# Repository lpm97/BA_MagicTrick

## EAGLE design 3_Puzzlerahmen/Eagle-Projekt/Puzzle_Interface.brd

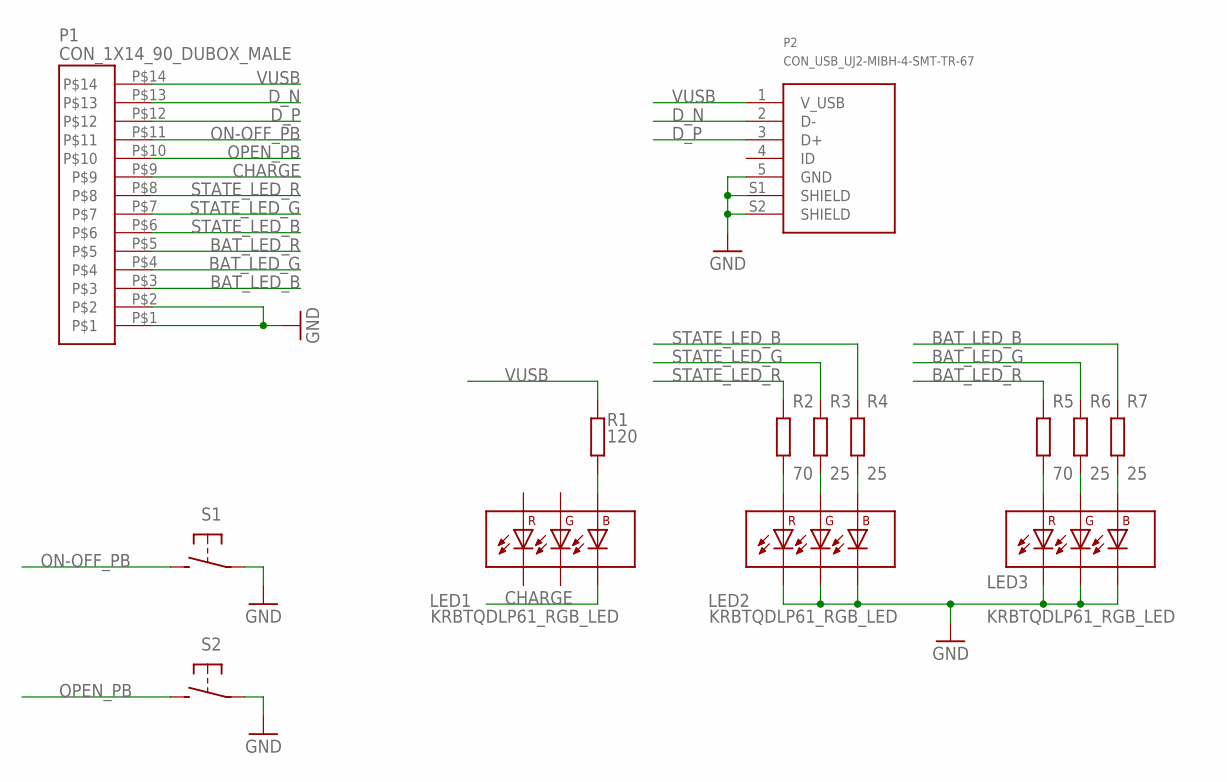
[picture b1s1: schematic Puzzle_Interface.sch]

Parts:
LED1, LED2, LED3: KRBTQDLP61_RGB_LED
P1: CON_1X14_90_DUBOX_MALE
P2: CON_USB_UJ2-MIBH-4-SMT-TR-67
R1: 120; 0603
R2, R5: 70; 0603
R3, R4, R6, R7: 25; 0603
S1, S2: EG5358CT-ND_PB

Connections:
BAT_LED_B: P1.P$3, R7.2
BAT_LED_G: P1.P$4, R6.2
BAT_LED_R: P1.P$5, R5.2
CHARGE: LED1.P$4 (BC), P1.P$9
D_N: P1.P$13, P2.2 (D-)
D_P: P1.P$12, P2.3 (D+)
GND: LED2.P$3 (GC), LED2.P$4 (BC), LED2.P$6 (RC), LED3.P$3 (GC), LED3.P$4 (BC), LED3.P$6 (RC), P1.P$1, P1.P$2, P2.5 (GND), P2.S1 (SHIELD), P2.S2 (SHIELD), S1.1, S1.S1, S1.S2, S2.1, S2.S1, S2.S2
unnamed: LED1.P$2 (BA), R1.1
unnamed: LED2.P$5 (RA), R2.1
unnamed: LED2.P$1 (GA), R3.1
unnamed: LED2.P$2 (BA), R4.1
unnamed: LED3.P$5 (RA), R5.1
unnamed: LED3.P$1 (GA), R6.1
unnamed: LED3.P$2 (BA), R7.1
ON-OFF_PB: P1.P$11, S1.2 (S)
OPEN_PB: P1.P$10, S2.2 (S)
STATE_LED_B: P1.P$6, R4.2
STATE_LED_G: P1.P$7, R3.2
STATE_LED_R: P1.P$8, R2.2
VUSB: P1.P$14, P2.1 (V_USB), R1.2

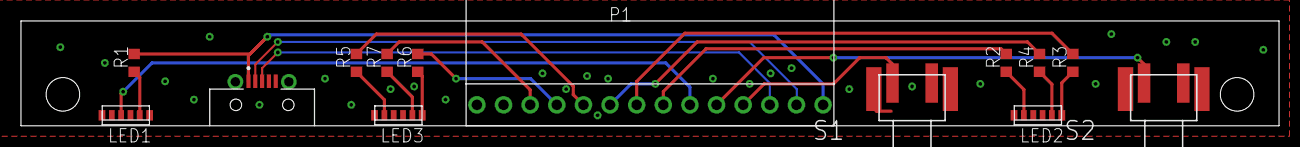
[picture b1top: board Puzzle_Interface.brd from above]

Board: 2 copper layers, 120.0 x 10.0 mm, 14 parts (0 on the bottom side), 20 nets.

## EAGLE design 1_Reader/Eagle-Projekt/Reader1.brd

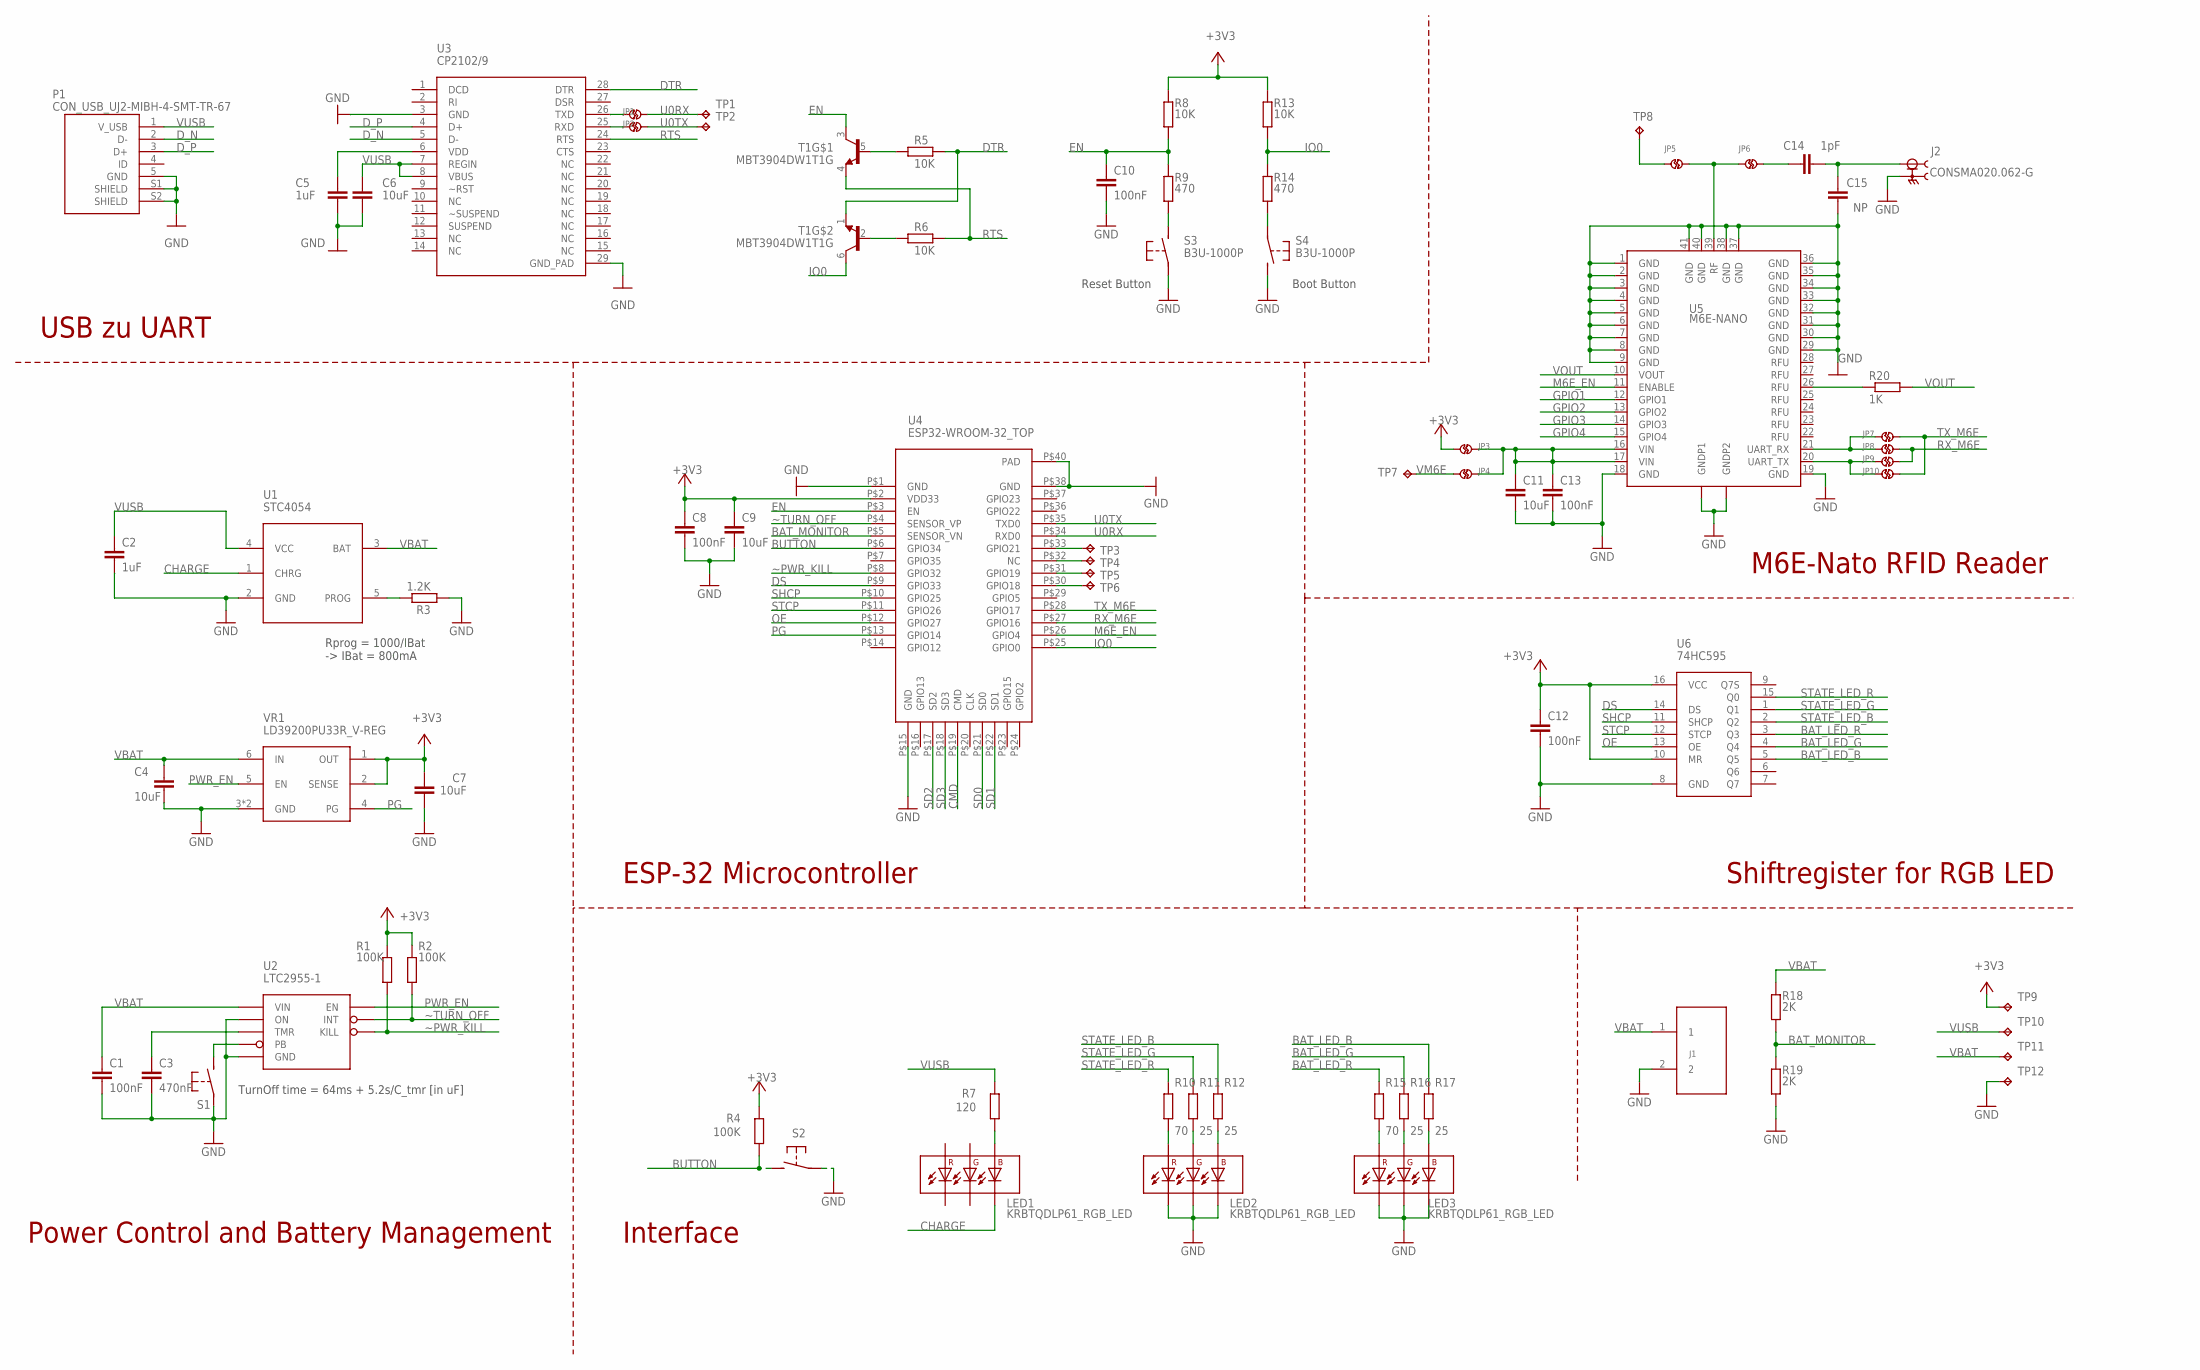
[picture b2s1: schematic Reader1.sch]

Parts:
C1, C8, C10, C12, C13: 100nF; 0603
C2, C5: 1uF; 0603
C3: 470nF; 0603
C4, C6, C7, C9, C11: 10uF; 0603
C14: 1pF; 0603
C15: NP; 0603
J1: CON_2
J2: CONSMA020.062-G; LINX_CONSMA020.062-G
JP1, JP2, JP3, JP4, JP5, JP6, JP7, JP8, JP9, JP10: SOLDER_JUMPER
LED1, LED2, LED3: KRBTQDLP61_RGB_LED
P1: CON_USB_UJ2-MIBH-4-SMT-TR-67
R1, R2, R4: 100K; 0603
R3: 1.2K; 0603
R5, R6, R8, R13: 10K; 0603
R7: 120; 0603
R9, R14: 470; 0603
R10, R15: 70; 0603
R11, R12, R16, R17: 25; 0603
R18, R19: 2K; 0603
R20: 1K; 0603
S1, S2: EG5358CT-ND_PB
S3, S4: B3U-1000P
T1: MBT3904DW1T1G; SOT23-6
TP1, TP2, TP3, TP4, TP5, TP6, TP7, TP8, TP9, TP10, TP11, TP12: TP; TEST_PAD
U1: STC4054; TSOT23-5L
U2: LTC2955-1; SOT23-8
U3: CP2102/9; QFN-28
U4: ESP32-WROOM-32_TOP
U5: M6E-NANO
U6: 74HC595; SOIC-16
VR1: LD39200PU33R_V-REG; DFN-6

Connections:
+3V3: C7.2, C8.1, C9.1, C12.1, JP3.P$1, R1.1, R2.1, R4.2, R8.2, R13.2, TP9.TP, U4.P$2 (VDD33), U6.10 (MR), U6.16 (VCC), VR1.1 (OUT), VR1.2 (SENSE)
BAT_LED_B: R17.2, U6.5 (Q5)
BAT_LED_G: R16.2, U6.4 (Q4)
BAT_LED_R: R15.2, U6.3 (Q3)
BAT_MONITOR: R18.2, R19.1, U4.P$5 (SENSOR_VN)
BUTTON: R4.1, S2.2 (S), U4.P$6 (GPIO34)
CHARGE: LED1.P$4 (BC), U1.1 (CHRG)
CMD: U4.P$19 (CMD)
DS: U4.P$9 (GPIO33), U6.14 (DS)
DTR: R5.1, T1.1 (E), U3.28 (DTR)
D_N: P1.2 (D-), U3.5 (D-)
D_P: P1.3 (D+), U3.4 (D+)
EN: C10.1, R8.1, R9.2, T1.3 (C), U4.P$3 (EN)
GND: C1.2, C2.2, C3.2, C4.2, C5.2, C6.2, C7.1, C8.2, C9.2, C10.2, C11.2, C12.2, C13.2, C15.1, J1.2, J2.S1 (2), J2.S2 (2), J2.S3 (2), J2.S4 (2), LED2.P$3 (GC), LED2.P$4 (BC), LED2.P$6 (RC), LED3.P$3 (GC), LED3.P$4 (BC), LED3.P$6 (RC), P1.5 (GND), P1.S1 (SHIELD), P1.S2 (SHIELD), R3.1, R19.2, S1.1, S1.S1, S1.S2, S2.1, S2.S1, S2.S2, S3.P$1, S4.P$2 (S), TP12.TP, U1.2 (GND), U2.1 (ON), U2.4 (GND), U3.3 (GND), U3.29 (GND_PAD), U4.P$1 (GND), U4.P$15 (GND), U4.P$38 (GND), U4.P$40 (PAD), U5.1 (GND), U5.2 (GND), U5.3 (GND), U5.4 (GND), U5.5 (GND), U5.6 (GND), U5.7 (GND), U5.8 (GND), U5.9 (GND), U5.18 (GND), U5.19 (GND), U5.29 (GND), U5.30 (GND), U5.31 (GND), U5.32 (GND), U5.33 (GND), U5.34 (GND), U5.35 (GND), U5.36 (GND), U5.37 (GND), U5.38 (GND), U5.40 (GND), U5.41 (GND), U5.GND_PAD1 (GNDP1), U5.GND_PAD2 (GNDP2), U6.8 (GND), VR1.3 (GND), VR1.7 (GND)
GPIO1: U5.12 (GPIO1)
GPIO2: U5.13 (GPIO2)
GPIO3: U5.14 (GPIO3)
GPIO4: U5.15 (GPIO4)
IO0: R13.1, R14.2, T1.6 (C), U4.P$25 (GPIO0)
M6E_EN: U4.P$26 (GPIO4), U5.11 (ENABLE)
unnamed: R20.1, U5.26 (RFU)
unnamed: JP5.P$2, JP6.P$1, U5.39 (RF)
unnamed: C14.1, JP6.P$2
unnamed: C14.2, C15.2, J2.1
unnamed: JP5.P$1, TP8.TP
unnamed: R5.2, T1.5 (B)
unnamed: R6.2, T1.2 (B)
unnamed: C5.1, U3.6 (VDD)
unnamed: LED3.P$5 (RA), R15.1
unnamed: R9.1, S3.P$2 (S)
unnamed: R14.1, S4.P$1
unnamed: C11.1, C13.1, JP3.P$2, JP4.P$2, U5.16 (VIN), U5.17 (VIN)
unnamed: LED2.P$5 (RA), R10.1
unnamed: LED1.P$2 (BA), R7.1
unnamed: LED2.P$1 (GA), R11.1
unnamed: LED2.P$2 (BA), R12.1
unnamed: LED3.P$1 (GA), R16.1
unnamed: R3.2, U1.5 (PROG)
unnamed: JP1.P$1, U3.26 (TXD)
unnamed: LED3.P$2 (BA), R17.1
unnamed: JP2.P$1, U3.25 (RXD)
unnamed: S1.2 (S), U2.5 (PB)
unnamed: TP5.TP, U4.P$31 (GPIO19)
unnamed: C3.1, U2.3 (TMR)
unnamed: TP6.TP, U4.P$30 (GPIO18)
unnamed: TP3.TP, U4.P$33 (GPIO21)
unnamed: TP4.TP, U4.P$32 (NC)
OE: U4.P$12 (GPIO27), U6.13 (OE)
PG: U4.P$13 (GPIO14), VR1.4 (PG)
PWR_EN: U2.7 (EN), VR1.5 (EN)
RTS: R6.1, T1.4 (E), U3.24 (RTS)
RXI: JP7.P$1, JP8.P$1, U5.21 (UART_RX)
RX_M6E: JP8.P$2, JP9.P$2, U4.P$27 (GPIO16)
SD0: U4.P$21 (SD0)
SD1: U4.P$22 (SD1)
SD2: U4.P$17 (SD2)
SD3: U4.P$18 (SD3)
SHCP: U4.P$10 (GPIO25), U6.11 (SHCP)
STATE_LED_B: R12.2, U6.2 (Q2)
STATE_LED_G: R11.2, U6.1 (Q1)
STATE_LED_R: R10.2, U6.15 (Q0)
STCP: U4.P$11 (GPIO26), U6.12 (STCP)
TXO: JP9.P$1, JP10.P$1, U5.20 (UART_TX)
TX_M6E: JP7.P$2, JP10.P$2, U4.P$28 (GPIO17)
U0RX: JP1.P$2, TP1.TP, U4.P$34 (RXD0)
U0TX: JP2.P$2, TP2.TP, U4.P$35 (TXD0)
VBAT: C1.1, C4.1, J1.1, R18.1, TP11.TP, U1.3 (BAT), U2.6 (VIN), VR1.6 (IN)
VM6E: JP4.P$1, TP7.TP
VOUT: R20.2, U5.10 (VOUT)
VUSB: C2.1, C6.1, P1.1 (V_USB), R7.2, TP10.TP, U1.4 (VCC), U3.7 (REGIN), U3.8 (VBUS)
~PWR_KILL: R1.2, U2.2 (KILL), U4.P$8 (GPIO32)
~TURN_OFF: R2.2, U2.8 (INT), U4.P$4 (SENSOR_VP)

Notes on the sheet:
Rprog = 1000/IBat -> IBat = 800mA
TurnOff time = 64ms + 5.2s/C_tmr [in uF]
Reset Button
Boot Button
Power Control and Battery Management
ESP-32 Microcontroller
USB zu UART
Interface
Shiftregister for RGB LED
M6E-Nato RFID Reader

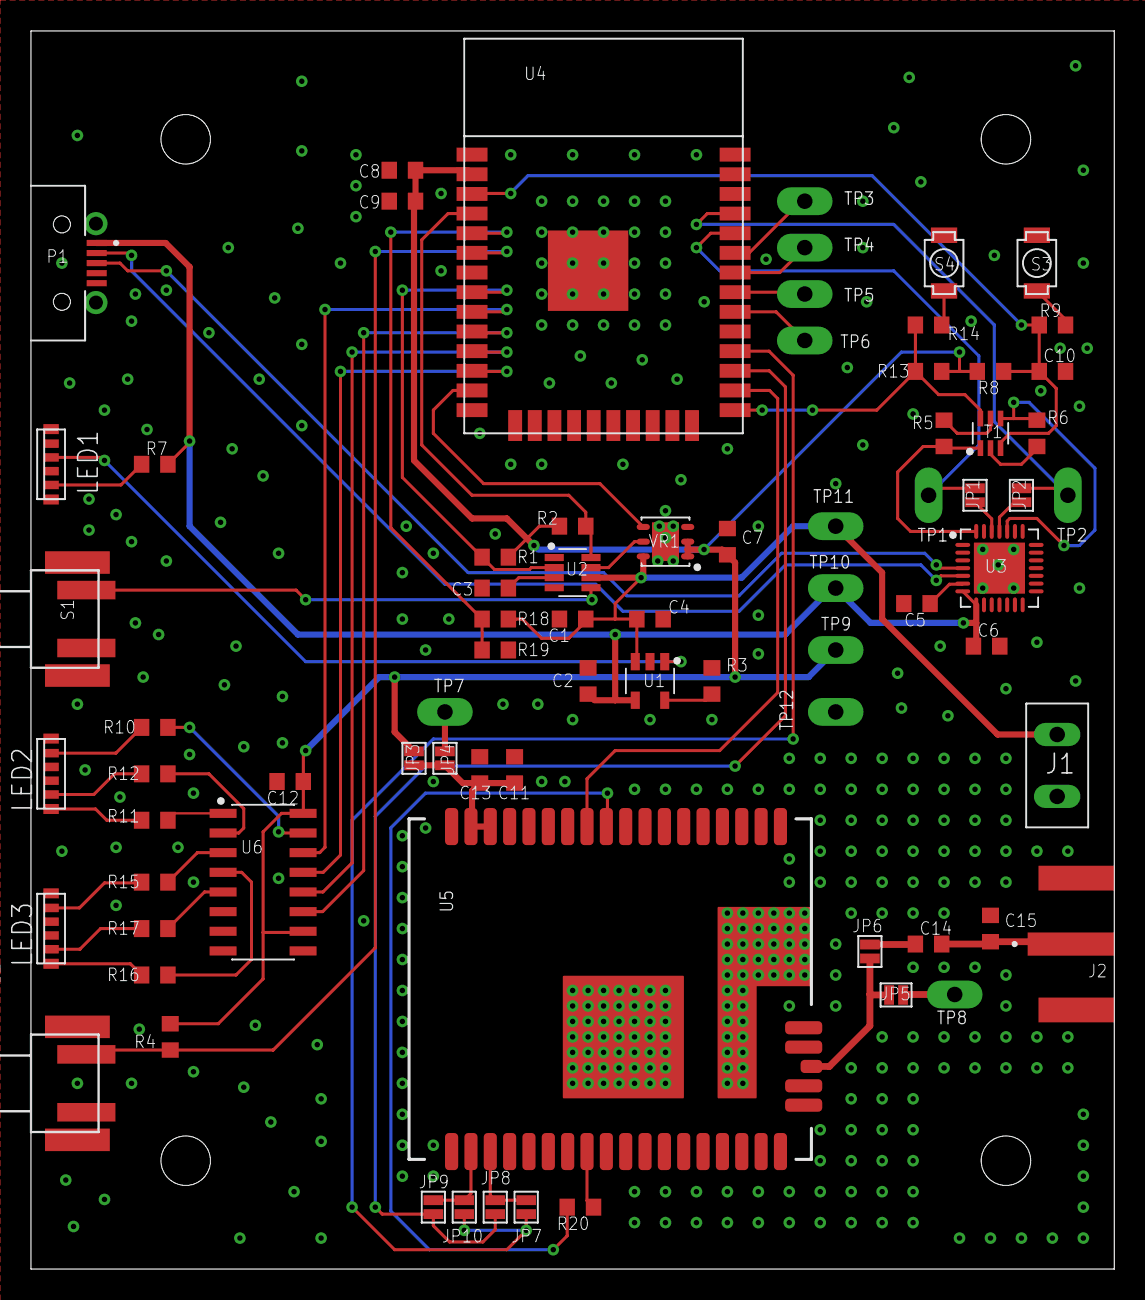
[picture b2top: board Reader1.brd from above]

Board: 2 copper layers, 70.0 x 80.0 mm, 75 parts (0 on the bottom side), 63 nets.

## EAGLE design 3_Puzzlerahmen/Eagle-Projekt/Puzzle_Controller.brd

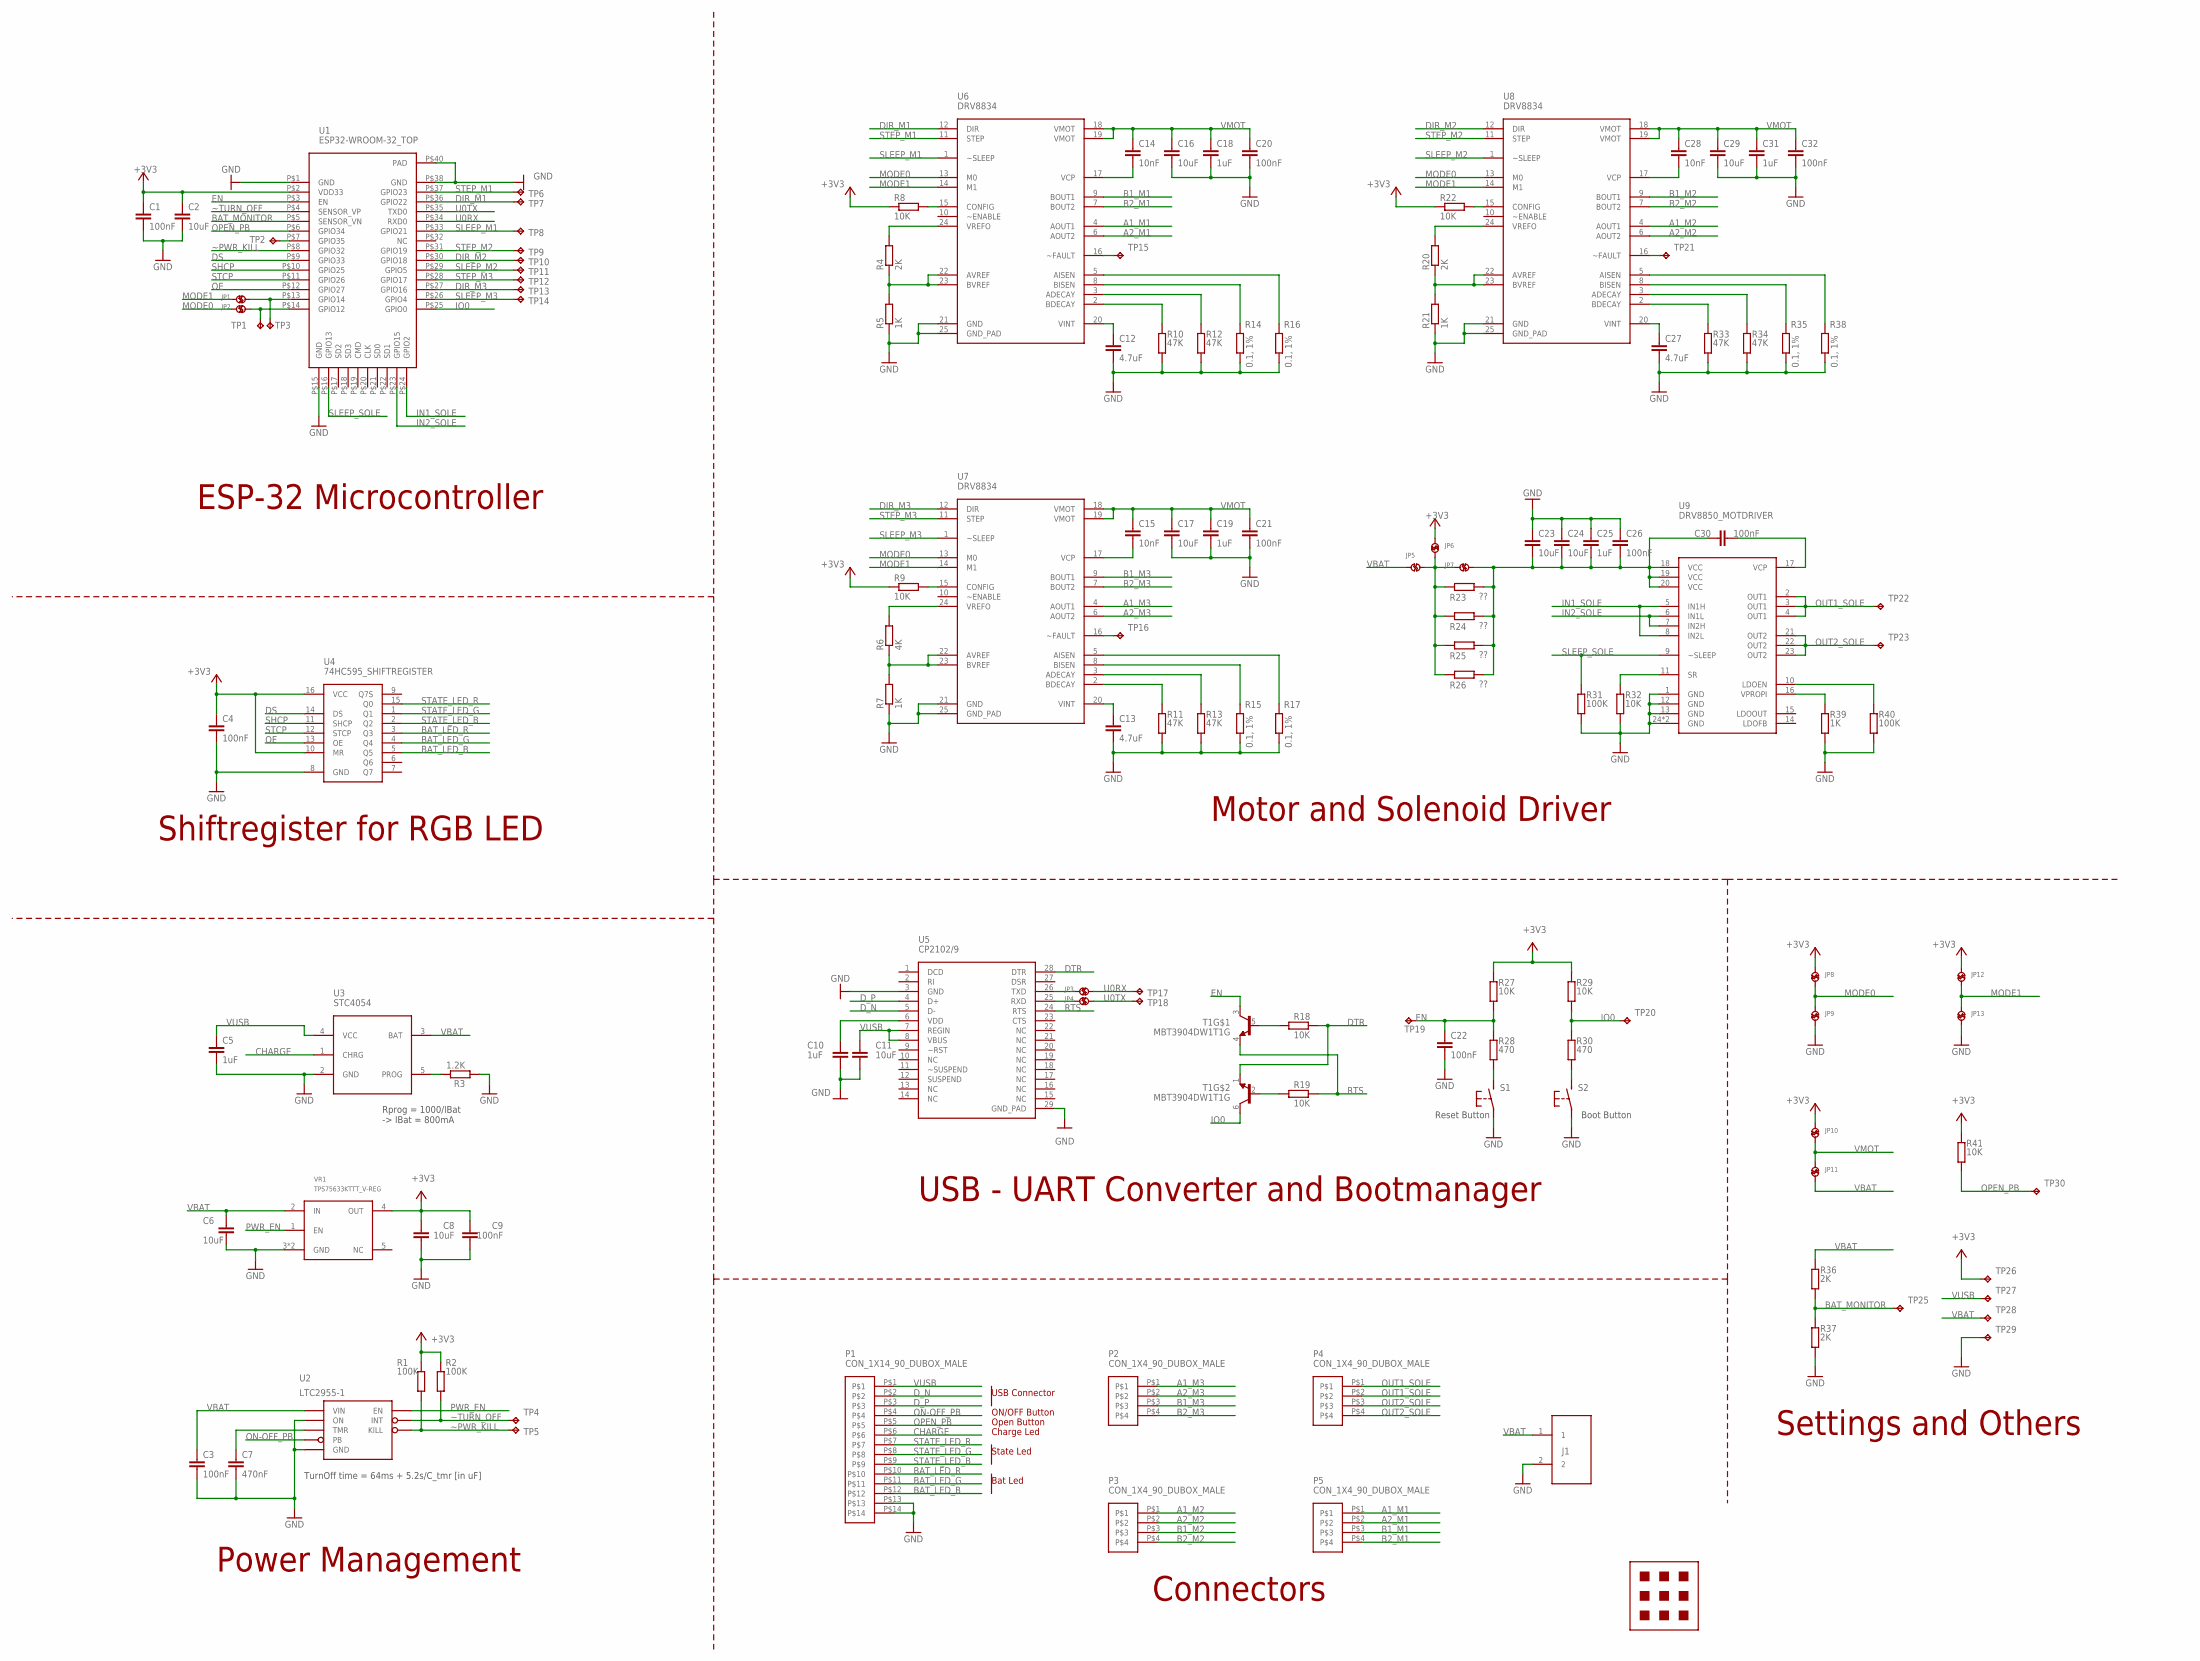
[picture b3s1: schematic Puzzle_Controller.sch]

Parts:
C1, C3, C4, C9, C20, C21, C22, C26, C30, C32: 100nF; 0603
C2, C6, C8, C11, C16, C17, C23, C24, C29: 10uF; 0603
C5, C10, C18, C19, C25, C31: 1uF; 0603
C7: 470nF; 0603
C12, C13, C27: 4.7uF; 0603
C14, C15, C28: 10nF; 0603
J1: CON_2
JP1, JP2, JP3, JP4, JP5, JP6, JP7, JP8, JP9, JP10, JP11, JP12, JP13: SOLDER_JUMPER
MEC1: FREESTYLE_PAD
P1: CON_1X14_90_DUBOX_MALE
P2, P3, P4, P5: CON_1X4_90_DUBOX_MALE
R1, R2, R31, R40: 100K; 0603
R3: 1.2K; 0603
R4, R20, R36, R37: 2K; 0603
R5, R7, R21, R39: 1K; 0603
R6: 4K; 0603
R8, R9, R18, R19, R22, R27, R29, R32, R41: 10K; 0603
R10, R11, R12, R13, R33, R34: 47K; 0603
R14, R15, R16, R17, R35, R38: 0.1, 1%; 0603
R23, R24, R25, R26: ??; 0603
R28, R30: 470; 0603
S1, S2: B3U-1000P
T1: MBT3904DW1T1G; SOT23-6
TP1, TP2, TP3, TP4, TP5, TP6, TP7, TP8, TP9, TP10, TP11, TP12, TP13, TP14, TP15, TP16, TP17, TP18, TP19, TP20, TP21, TP22, TP23, TP25, TP26, TP27, TP28, TP29, TP30: TP; TEST_PAD
U1: ESP32-WROOM-32_TOP
U2: LTC2955-1; SOT23-8
U3: STC4054; TSOT23-5L
U4: 74HC595_SHIFTREGISTER; SOIC-16
U5: CP2102/9; QFN-28
U6, U7, U8: DRV8834; TSSOP-24
U9: DRV8850_MOTDRIVER; QFN-24
VR1: TPS75633KTTT_V-REG

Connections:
+3V3: C1.1, C2.1, C4.1, C8.2, C9.2, JP6.P$2, JP8.P$1, JP10.P$1, JP12.P$1, R1.1, R2.1, R8.1, R9.1, R22.1, R27.2, R29.2, R41.2, TP26.TP, U1.P$2 (VDD33), U4.10 (MR), U4.16 (VCC), VR1.4 (OUT)
A1_M1: P5.P$1, U6.4 (AOUT1)
A1_M2: P3.P$1, U8.4 (AOUT1)
A1_M3: P2.P$1, U7.4 (AOUT1)
A2_M1: P5.P$2, U6.6 (AOUT2)
A2_M2: P3.P$2, U8.6 (AOUT2)
A2_M3: P2.P$2, U7.6 (AOUT2)
B1_M1: P5.P$3, U6.9 (BOUT1)
B1_M2: P3.P$3, U8.9 (BOUT1)
B1_M3: P2.P$3, U7.9 (BOUT1)
B2_M1: P5.P$4, U6.7 (BOUT2)
B2_M2: P3.P$4, U8.7 (BOUT2)
B2_M3: P2.P$4, U7.7 (BOUT2)
BAT_LED_B: P1.P$12, U4.5 (Q5)
BAT_LED_G: P1.P$11, U4.4 (Q4)
BAT_LED_R: P1.P$10, U4.3 (Q3)
BAT_MONITOR: R36.2, R37.1, TP25.TP, U1.P$5 (SENSOR_VN)
CHARGE: P1.P$6, U3.1 (CHRG)
DIR_M1: TP7.TP, U1.P$36 (GPIO22), U6.12 (DIR)
DIR_M2: TP10.TP, U1.P$30 (GPIO18), U8.12 (DIR)
DIR_M3: TP13.TP, U1.P$27 (GPIO16), U7.12 (DIR)
DS: U1.P$9 (GPIO33), U4.14 (DS)
DTR: R18.1, T1.1 (E), U5.28 (DTR)
D_N: P1.P$2, U5.5 (D-)
D_P: P1.P$3, U5.4 (D+)
EN: C22.1, R27.1, R28.2, T1.3 (C), TP19.TP, U1.P$3 (EN)
GND: C1.2, C2.2, C3.2, C4.2, C5.2, C6.2, C7.2, C8.1, C9.1, C10.2, C11.2, C12.2, C13.2, C16.2, C17.2, C18.2, C19.2, C20.2, C21.2, C22.2, C23.1, C24.1, C25.1, C26.1, C27.2, C29.2, C31.2, C32.2, J1.2, JP9.P$2, JP13.P$2, P1.P$13, P1.P$14, R3.1, R5.1, R7.1, R10.1, R11.1, R12.1, R13.1, R14.1, R15.1, R16.1, R17.1, R21.1, R31.1, R32.1, R33.1, R34.1, R35.1, R37.2, R38.1, R39.1, R40.1, S1.P$1, S2.P$1, TP29.TP, U1.P$1 (GND), U1.P$15 (GND), U1.P$38 (GND), U1.P$40 (PAD), U2.1 (ON), U2.4 (GND), U3.2 (GND), U4.8 (GND), U5.3 (GND), U5.29 (GND_PAD), U6.21 (GND), U6.25 (GND_PAD), U7.21 (GND), U7.25 (GND_PAD), U8.21 (GND), U8.25 (GND_PAD), U9.1 (GND), U9.12 (GND), U9.13 (GND), U9.24 (GND), U9.25 (GND), VR1.3 (GND), VR1.6 (GND)
IN1_SOLE: U1.P$24 (GPIO2), U9.5 (IN1H), U9.8 (IN2L)
IN2_SOLE: U1.P$23 (GPIO15), U9.6 (IN1L), U9.7 (IN2H)
IO0: R29.1, R30.2, T1.6 (C), TP20.TP, U1.P$25 (GPIO0)
MODE0: JP2.P$1, JP8.P$2, JP9.P$1, U6.13 (M0), U7.13 (M0), U8.13 (M0)
MODE1: JP1.P$1, JP12.P$2, JP13.P$1, U6.14 (M1), U7.14 (M1), U8.14 (M1)
unnamed: R28.1, S1.P$2 (S)
unnamed: R8.2, U6.15 (CONFIG)
unnamed: R30.1, S2.P$2 (S)
unnamed: R18.2, T1.5 (B)
unnamed: R19.2, T1.2 (B)
unnamed: C10.1, U5.6 (VDD)
unnamed: R4.1, R5.2, U6.22 (AVREF), U6.23 (BVREF)
unnamed: R4.2, U6.24 (VREFO)
unnamed: C14.2, U6.17 (VCP)
unnamed: C12.1, U6.20 (VINT)
unnamed: JP3.P$1, U5.26 (TXD)
unnamed: R10.2, U6.2 (BDECAY)
unnamed: R12.2, U6.3 (ADECAY)
unnamed: R14.2, U6.8 (BISEN)
unnamed: R16.2, U6.5 (AISEN)
unnamed: JP5.P$1, JP6.P$1, JP7.P$1, R23.1, R24.1, R25.1, R26.1
unnamed: TP15.TP, U6.16 (~FAULT)
unnamed: JP4.P$1, U5.25 (RXD)
unnamed: R3.2, U3.5 (PROG)
unnamed: TP2.TP, U1.P$7 (GPIO35)
unnamed: R22.2, U8.15 (CONFIG)
unnamed: C23.2, C24.2, C25.2, C26.2, C30.1, JP7.P$2, R23.2, R24.2, R25.2, R26.2, U9.18 (VCC), U9.19 (VCC), U9.20 (VCC)
unnamed: JP1.P$2, TP3.TP, U1.P$13 (GPIO14)
unnamed: C7.1, U2.3 (TMR)
unnamed: R20.1, R21.2, U8.22 (AVREF), U8.23 (BVREF)
unnamed: R20.2, U8.24 (VREFO)
unnamed: C28.2, U8.17 (VCP)
unnamed: TP21.TP, U8.16 (~FAULT)
unnamed: C27.1, U8.20 (VINT)
unnamed: R33.2, U8.2 (BDECAY)
unnamed: R34.2, U8.3 (ADECAY)
unnamed: R35.2, U8.8 (BISEN)
unnamed: R38.2, U8.5 (AISEN)
unnamed: R9.2, U7.15 (CONFIG)
unnamed: R6.1, R7.2, U7.22 (AVREF), U7.23 (BVREF)
unnamed: R6.2, U7.24 (VREFO)
unnamed: C15.2, U7.17 (VCP)
unnamed: TP16.TP, U7.16 (~FAULT)
unnamed: C13.1, U7.20 (VINT)
unnamed: R11.2, U7.2 (BDECAY)
unnamed: R13.2, U7.3 (ADECAY)
unnamed: R15.2, U7.8 (BISEN)
unnamed: R17.2, U7.5 (AISEN)
unnamed: R39.2, U9.16 (VPROPI)
unnamed: R32.2, U9.11 (SR)
unnamed: C30.2, U9.17 (VCP)
unnamed: R40.2, U9.10 (LDOEN)
unnamed: JP2.P$2, TP1.TP, U1.P$14 (GPIO12)
OE: U1.P$12 (GPIO27), U4.13 (OE)
ON-OFF_PB: P1.P$4, U2.5 (PB)
OPEN_PB: P1.P$5, R41.1, TP30.TP, U1.P$6 (GPIO34)
OUT1_SOLE: P4.P$1, P4.P$2, TP22.TP, U9.2 (OUT1), U9.3 (OUT1), U9.4 (OUT1)
OUT2_SOLE: P4.P$3, P4.P$4, TP23.TP, U9.21 (OUT2), U9.22 (OUT2), U9.23 (OUT2)
PWR_EN: U2.7 (EN), VR1.1 (EN)
RTS: R19.1, T1.4 (E), U5.24 (RTS)
SHCP: U1.P$10 (GPIO25), U4.11 (SHCP)
SLEEP_M1: TP8.TP, U1.P$33 (GPIO21), U6.1 (~SLEEP)
SLEEP_M2: TP11.TP, U1.P$29 (GPIO5), U8.1 (~SLEEP)
SLEEP_M3: TP14.TP, U1.P$26 (GPIO4), U7.1 (~SLEEP)
SLEEP_SOLE: R31.2, U1.P$16 (GPIO13), U9.9 (~SLEEP)
STATE_LED_B: P1.P$9, U4.2 (Q2)
STATE_LED_G: P1.P$8, U4.1 (Q1)
STATE_LED_R: P1.P$7, U4.15 (Q0)
STCP: U1.P$11 (GPIO26), U4.12 (STCP)
STEP_M1: TP6.TP, U1.P$37 (GPIO23), U6.11 (STEP)
STEP_M2: TP9.TP, U1.P$31 (GPIO19), U8.11 (STEP)
STEP_M3: TP12.TP, U1.P$28 (GPIO17), U7.11 (STEP)
U0RX: JP3.P$2, TP17.TP, U1.P$34 (RXD0)
U0TX: JP4.P$2, TP18.TP, U1.P$35 (TXD0)
VBAT: C3.1, C6.1, J1.1, JP5.P$2, JP11.P$2, R36.1, TP28.TP, U2.6 (VIN), U3.3 (BAT), VR1.2 (IN)
VMOT: C14.1, C15.1, C16.1, C17.1, C18.1, C19.1, C20.1, C21.1, C28.1, C29.1, C31.1, C32.1, JP10.P$2, JP11.P$1, U6.18 (VMOT), U6.19 (VMOT), U7.18 (VMOT), U7.19 (VMOT), U8.18 (VMOT), U8.19 (VMOT)
VUSB: C5.1, C11.1, P1.P$1, TP27.TP, U3.4 (VCC), U5.7 (REGIN), U5.8 (VBUS)
~PWR_KILL: R1.2, TP5.TP, U1.P$8 (GPIO32), U2.2 (KILL)
~TURN_OFF: R2.2, TP4.TP, U1.P$4 (SENSOR_VP), U2.8 (INT)

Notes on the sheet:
Reset Button
Boot Button
Rprog = 1000/IBat -> IBat = 800mA
TurnOff time = 64ms + 5.2s/C_tmr [in uF]
Charge Led
State Led
ON/OFF Button
Open Button
Bat Led
USB Connector
ESP-32 Microcontroller
Shiftregister for RGB LED
Power Management
Connectors
USB - UART Converter and Bootmanager
Settings and Others
Motor and Solenoid Driver

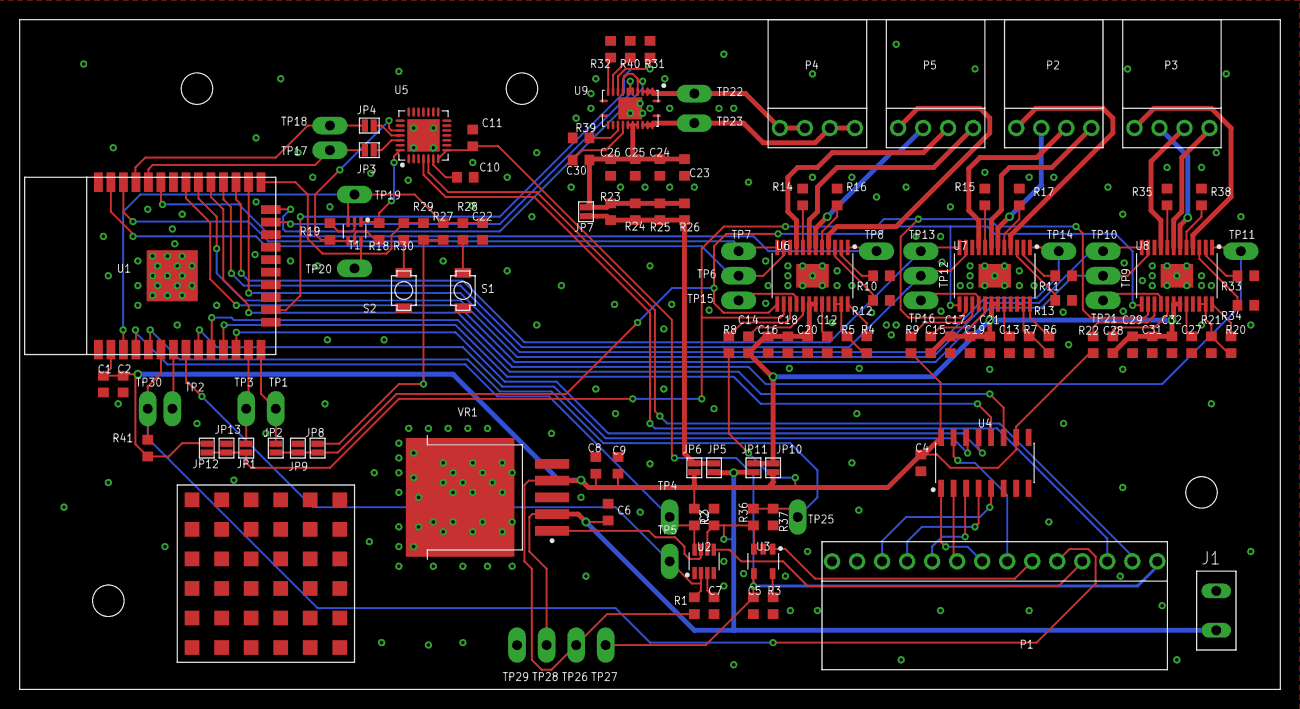
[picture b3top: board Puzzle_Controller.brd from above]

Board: 2 copper layers, 128.0 x 68.0 mm, 135 parts (0 on the bottom side), 106 nets.

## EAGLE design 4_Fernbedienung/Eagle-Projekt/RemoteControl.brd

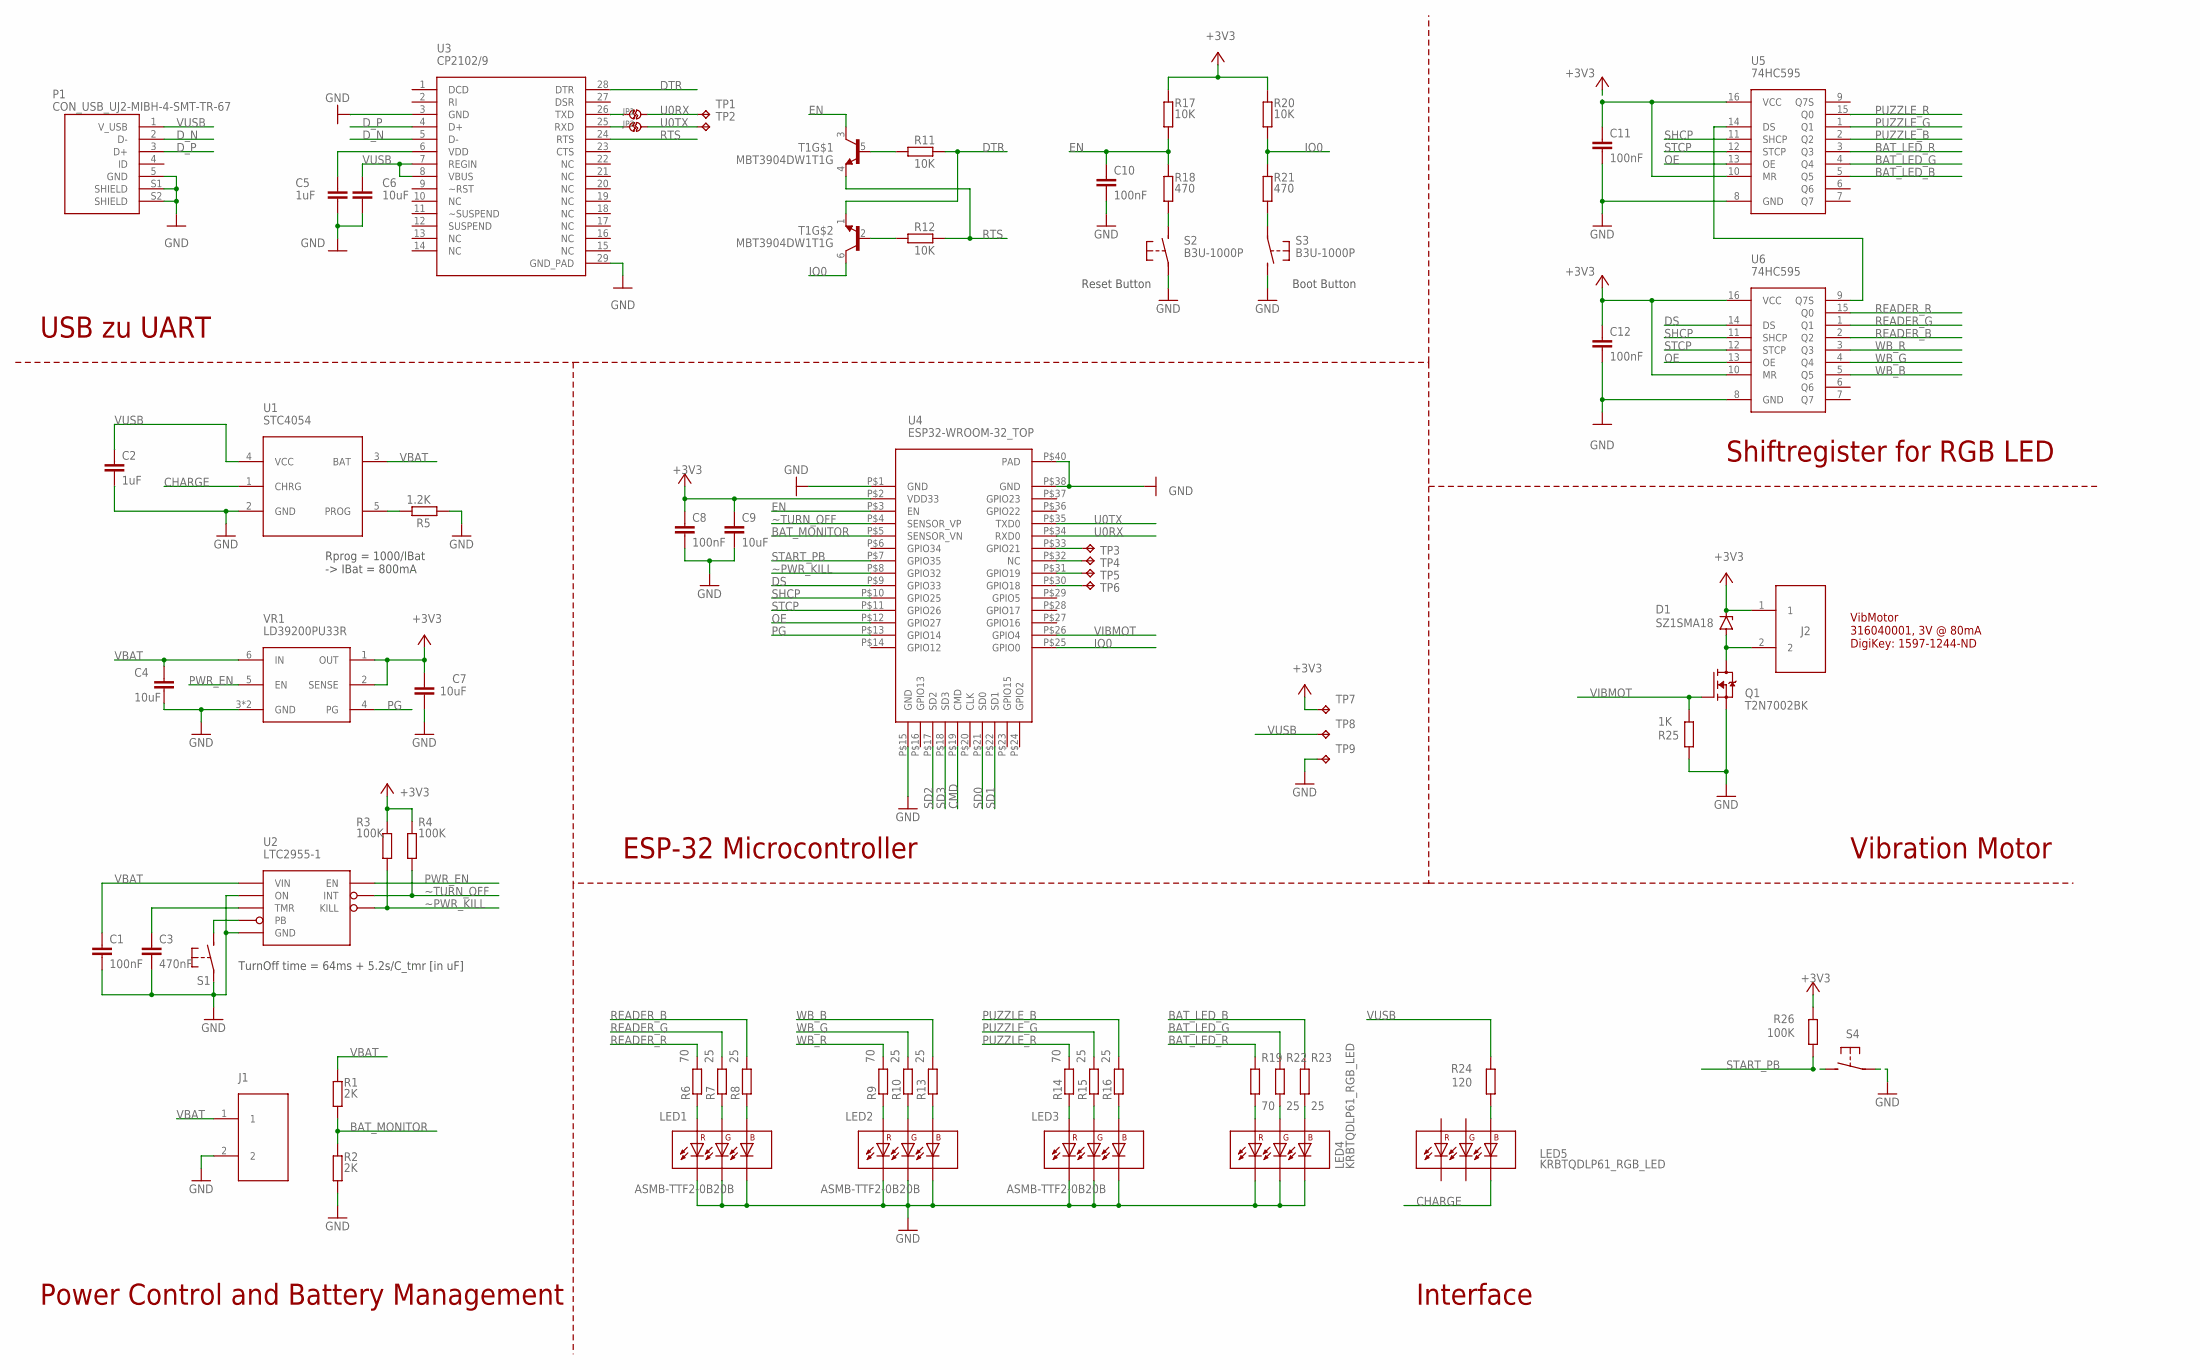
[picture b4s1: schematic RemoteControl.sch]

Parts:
C1, C8, C10, C11, C12: 100nF; 0603
C2, C5: 1uF; 0603
C3: 470nF; 0603
C4, C6, C7, C9: 10uF; 0603
D1: SZ1SMA18; SMA-2
J1, J2: CON_2
JP1, JP2: SOLDER_JUMPER
LED1, LED2, LED3: ASMB-TTF2-0B20B; ASMB-TTF2-0B20B_RGB_LED
LED4, LED5: KRBTQDLP61_RGB_LED
P1: CON_USB_UJ2-MIBH-4-SMT-TR-67
Q1: T2N7002BK; SOT23-3
R1, R2: 2K; 0603
R3, R4, R26: 100K; 0603
R5: 1.2K; 0603
R6, R9, R14, R19: 70; 0603
R7, R8, R10, R13, R15, R16, R22, R23: 25; 0603
R11, R12, R17, R20: 10K; 0603
R18, R21: 470; 0603
R24: 120; 0603
R25: 1K; 0603
S1: EG5358CT-ND_PB
S2, S3: B3U-1000P
S4: TL3313AF160QG_2
T1: MBT3904DW1T1G; SOT23-6
TP1, TP2, TP3, TP4, TP5, TP6, TP7, TP8, TP9: TP; TEST_PAD
U1: STC4054; TSOT23-5L
U2: LTC2955-1; SOT23-8
U3: CP2102/9; QFN-28
U4: ESP32-WROOM-32_TOP
U5, U6: 74HC595; SOIC-16
VR1: LD39200PU33R; DFN-6

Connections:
+3V3: C7.2, C8.1, C9.1, C11.1, C12.1, D1.1 (C), J2.1, R3.1, R4.1, R17.2, R20.2, R26.2, TP7.TP, U4.P$2 (VDD33), U5.10 (MR), U5.16 (VCC), U6.10 (MR), U6.16 (VCC), VR1.1 (OUT), VR1.2 (SENSE)
BAT_LED_B: R23.2, U5.5 (Q5)
BAT_LED_G: R22.2, U5.4 (Q4)
BAT_LED_R: R19.2, U5.3 (Q3)
BAT_MONITOR: R1.2, R2.1, U4.P$5 (SENSOR_VN)
CHARGE: LED5.P$4 (BC), U1.1 (CHRG)
CMD: U4.P$19 (CMD)
DS: U4.P$9 (GPIO33), U6.14 (DS)
DTR: R11.1, T1.1 (E), U3.28 (DTR)
D_N: P1.2 (D-), U3.5 (D-)
D_P: P1.3 (D+), U3.4 (D+)
EN: C10.1, R17.1, R18.2, T1.3 (C), U4.P$3 (EN)
GND: C1.2, C2.2, C3.2, C4.2, C5.2, C6.2, C7.1, C8.2, C9.2, C10.2, C11.2, C12.2, J1.2, LED1.BC, LED1.GC, LED1.RC, LED2.BC, LED2.GC, LED2.RC, LED3.BC, LED3.GC, LED3.RC, LED4.P$3 (GC), LED4.P$4 (BC), LED4.P$6 (RC), P1.5 (GND), P1.S1 (SHIELD), P1.S2 (SHIELD), Q1.2 (S), R2.2, R5.1, R25.1, S1.1, S1.S1, S1.S2, S2.P$1, S3.P$2 (S), S4.1, S4.2, TP9.TP, U1.2 (GND), U2.1 (ON), U2.4 (GND), U3.3 (GND), U3.29 (GND_PAD), U4.P$1 (GND), U4.P$15 (GND), U4.P$38 (GND), U4.P$40 (PAD), U5.8 (GND), U6.8 (GND), VR1.3 (GND), VR1.7 (GND)
IO0: R20.1, R21.2, T1.6 (C), U4.P$25 (GPIO0)
unnamed: U5.14 (DS), U6.9 (Q7S)
unnamed: D1.2 (A), J2.2, Q1.3 (D)
unnamed: R11.2, T1.5 (B)
unnamed: R12.2, T1.2 (B)
unnamed: C5.1, U3.6 (VDD)
unnamed: LED4.P$5 (RA), R19.1
unnamed: R18.1, S2.P$2 (S)
unnamed: R21.1, S3.P$1
unnamed: LED5.P$2 (BA), R24.1
unnamed: LED4.P$1 (GA), R22.1
unnamed: R5.2, U1.5 (PROG)
unnamed: JP1.P$1, U3.26 (TXD)
unnamed: LED4.P$2 (BA), R23.1
unnamed: JP2.P$1, U3.25 (RXD)
unnamed: S1.2 (S), U2.5 (PB)
unnamed: TP5.TP, U4.P$31 (GPIO19)
unnamed: C3.1, U2.3 (TMR)
unnamed: TP6.TP, U4.P$30 (GPIO18)
unnamed: TP3.TP, U4.P$33 (GPIO21)
unnamed: LED2.RA, R9.1
unnamed: TP4.TP, U4.P$32 (NC)
unnamed: LED2.GA, R10.1
unnamed: LED2.BA, R13.1
unnamed: LED3.RA, R14.1
unnamed: LED3.GA, R15.1
unnamed: LED3.BA, R16.1
unnamed: LED1.RA, R6.1
unnamed: LED1.GA, R7.1
unnamed: LED1.BA, R8.1
OE: U4.P$12 (GPIO27), U5.13 (OE), U6.13 (OE)
PG: U4.P$13 (GPIO14), VR1.4 (PG)
PUZZLE_B: R16.2, U5.2 (Q2)
PUZZLE_G: R15.2, U5.1 (Q1)
PUZZLE_R: R14.2, U5.15 (Q0)
PWR_EN: U2.7 (EN), VR1.5 (EN)
READER_B: R8.2, U6.2 (Q2)
READER_G: R7.2, U6.1 (Q1)
READER_R: R6.2, U6.15 (Q0)
RTS: R12.1, T1.4 (E), U3.24 (RTS)
SD0: U4.P$21 (SD0)
SD1: U4.P$22 (SD1)
SD2: U4.P$17 (SD2)
SD3: U4.P$18 (SD3)
SHCP: U4.P$10 (GPIO25), U5.11 (SHCP), U6.11 (SHCP)
START_PB: R26.1, S4.3 (S), S4.4 (S), U4.P$7 (GPIO35)
STCP: U4.P$11 (GPIO26), U5.12 (STCP), U6.12 (STCP)
U0RX: JP1.P$2, TP1.TP, U4.P$34 (RXD0)
U0TX: JP2.P$2, TP2.TP, U4.P$35 (TXD0)
VBAT: C1.1, C4.1, J1.1, R1.1, U1.3 (BAT), U2.6 (VIN), VR1.6 (IN)
VIBMOT: Q1.1 (G), R25.2, U4.P$26 (GPIO4)
VUSB: C2.1, C6.1, P1.1 (V_USB), R24.2, TP8.TP, U1.4 (VCC), U3.7 (REGIN), U3.8 (VBUS)
WB_B: R13.2, U6.5 (Q5)
WB_G: R10.2, U6.4 (Q4)
WB_R: R9.2, U6.3 (Q3)
~PWR_KILL: R3.2, U2.2 (KILL), U4.P$8 (GPIO32)
~TURN_OFF: R4.2, U2.8 (INT), U4.P$4 (SENSOR_VP)

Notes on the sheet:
Rprog = 1000/IBat -> IBat = 800mA
TurnOff time = 64ms + 5.2s/C_tmr [in uF]
Reset Button
Boot Button
Power Control and Battery Management
ESP-32 Microcontroller
USB zu UART
Shiftregister for RGB LED
VibMotor 316040001, 3V @ 80mA DigiKey: 1597-1244-ND
Interface
Vibration Motor
